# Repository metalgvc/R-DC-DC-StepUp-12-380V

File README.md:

Inverter 12v - 380v
Push-Pull 
TL494 module with MOSFET drivers
MOSFET IRF3205

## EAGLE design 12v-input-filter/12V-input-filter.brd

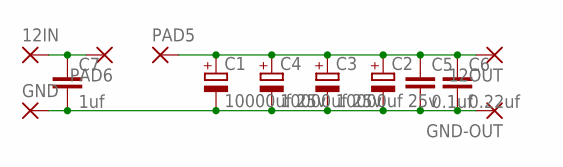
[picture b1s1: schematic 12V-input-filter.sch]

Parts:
12IN, 12OUT: 3,81/1,4
C1, C3, C4: 10000uf 25v; EB22,5D
C2: CPOL-EUE10-22.5; EB22,5D
C5: 0.1uf; C150-064X183
C6: 0.22uf; C150-064X183
C7: 1uf; C150-064X183
GND: 3,81/1,4
GND-OUT: 3,81/1,4
PAD5, PAD6: 3,81/1,4

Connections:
unnamed: C1.-, C2.-, C3.-, C4.-, C5.2, C6.2, C7.2, GND.1, GND-OUT.1
unnamed: 12OUT.1, C1.+, C2.+, C3.+, C4.+, C5.1, C6.1, PAD5.1
unnamed: 12IN.1, C7.1, PAD6.1

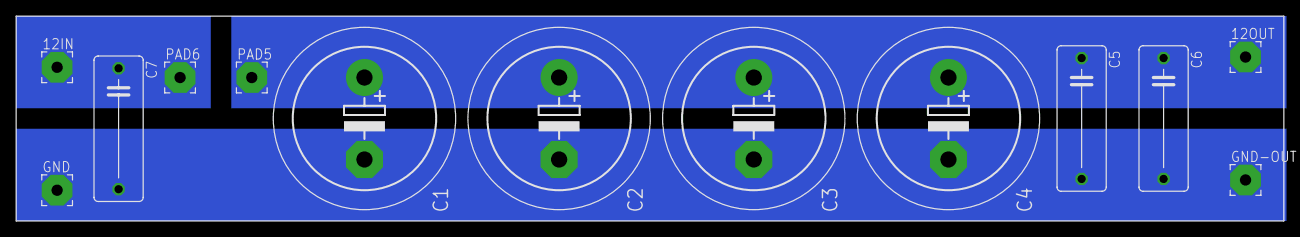
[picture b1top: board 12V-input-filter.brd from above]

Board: 2 copper layers, 157.2 x 25.4 mm, 13 parts (0 on the bottom side), 3 nets.

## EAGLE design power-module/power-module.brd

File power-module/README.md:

resistors 0.25W:
22 - 4
2k - 2

resistors 2W:
22 - 2
4k7 - 1
68k - 1

transistors:
IRF3205 - 4

diodes:
UF4007 - 4
shottky 60A300CT - 2

capacitors:
0.01uf (103) 400V - 2
0.1uf (104) 400V - 1
0.22uf (224) 400V(?) - 1

capacitors pol.:
470uf 200V - 4

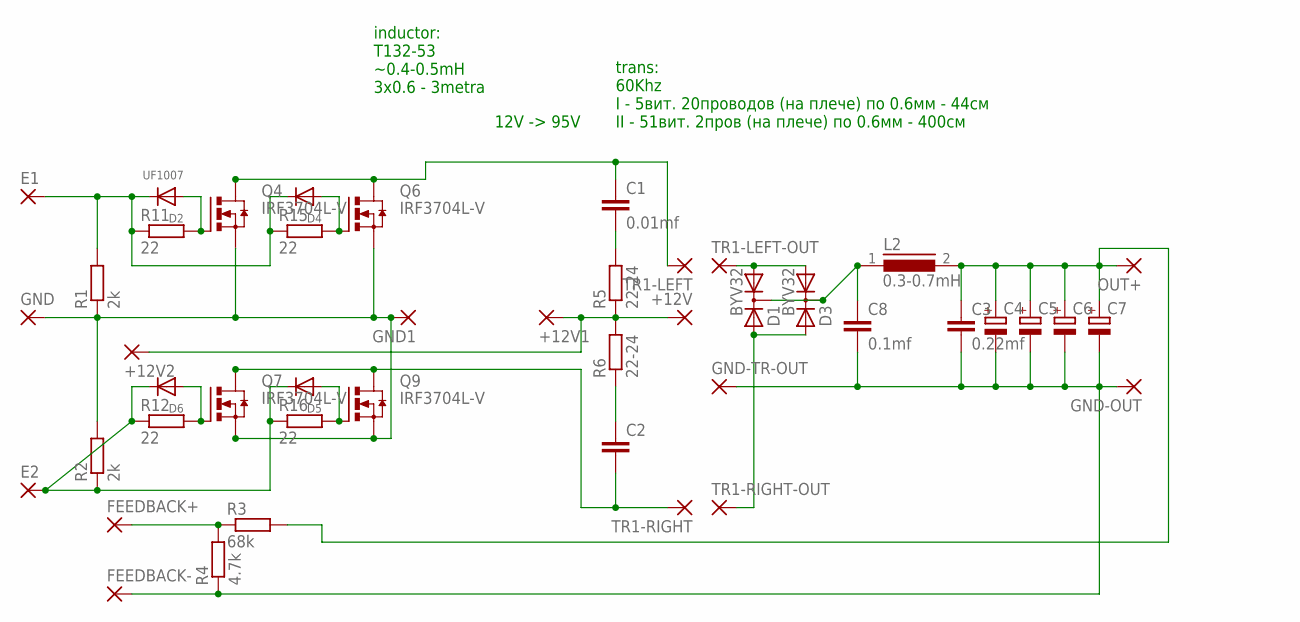
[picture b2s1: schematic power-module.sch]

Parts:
+12V, +12V1, +12V2: 3,81/1,1
C1: 0.01mf; C102-064X133
C2: C-EU102-064X133; C102-064X133
C3: 0.22mf; C150-064X183
C4, C5, C6, C7: CPOL-EUE10-22.5; EB22,5D
C8: 0.1mf; C150-064X183
D1, D3: BYV32; TO220ABS
D2: UF1007; DO-1N4148
D4, D5, D6: DIODEDO-1N4148; DO-1N4148
E1, E2: 3,81/1,1
FEEDBACK+: 3,81/1,1
FEEDBACK-: 3,81/1,1
GND, GND1: 3,81/1,1
GND-OUT: 3,81/1,1
GND-TR-OUT: 3,81/1,1
L2: 0.3-0.7mH; 11-27
OUT+: 3,81/1,1
Q4, Q6, Q7, Q9: IRF3704L-V; TO262-V
R1, R2: 2k; 0204/7
R3: 68k; 0617/17
R4: 4.7k; 0617/17
R5, R6: 22-24; P0613/15
R11, R12, R15, R16: 22; 0204/7
TR1-LEFT, TR1-LEFT-OUT, TR1-RIGHT, TR1-RIGHT-OUT: 3,81/1,1

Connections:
unnamed: GND.1, GND1.1, Q4.3 (S), Q6.3 (S), Q7.3 (S), Q9.3 (S), R1.1, R2.2
unnamed: C1.1, Q4.2 (D), Q6.2 (D), TR1-LEFT.1
unnamed: D5.C, D6.C, E2.1, R2.1, R12.1, R16.1
unnamed: FEEDBACK+.1, R3.1, R4.2
unnamed: +12V.1, +12V1.1, +12V2.1, R5.1, R6.2
unnamed: C3.2, C4.-, C5.-, C6.-, C7.-, C8.2, FEEDBACK-.1, GND-OUT.1, GND-TR-OUT.1, R4.1
unnamed: C2.2, Q7.2 (D), Q9.2 (D), TR1-RIGHT.1
unnamed: D2.C, D4.C, E1.1, R1.2, R11.1, R15.1
unnamed: C1.2, R5.2
unnamed: D1.A2, D3.A2, TR1-RIGHT-OUT.1
unnamed: C2.1, R6.1
unnamed: D1.A1, D3.A1, TR1-LEFT-OUT.1
unnamed: C8.1, D1.C, D3.C, L2.1
unnamed: C3.1, C4.+, C5.+, C6.+, C7.+, L2.2, OUT+.1, R3.2
unnamed: D2.A, Q4.1 (G), R11.2
unnamed: D6.A, Q7.1 (G), R12.2
unnamed: D4.A, Q6.1 (G), R15.2
unnamed: D5.A, Q9.1 (G), R16.2

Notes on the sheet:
12V -> 95V
trans: 60Khz I - 5вит. 20проводов (на плече) по 0.6мм - 44см II - 51вит. 2пров (на плече) по 0.6мм - 400см
inductor: T132-53 ~0.4-0.5mH 3x0.6 - 3metra

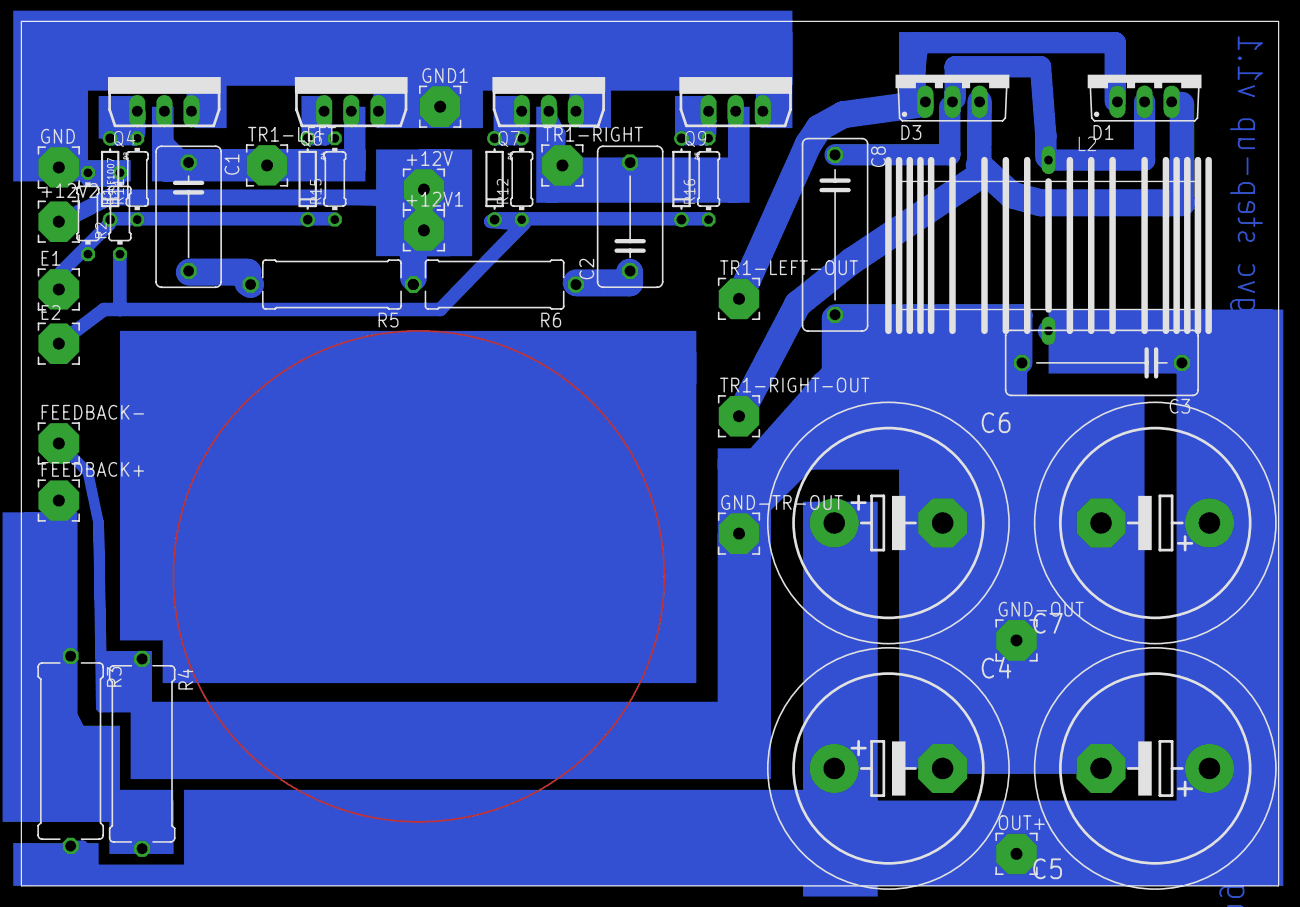
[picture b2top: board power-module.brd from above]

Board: 2 copper layers, 117.8 x 81.0 mm, 45 parts (0 on the bottom side), 18 nets.

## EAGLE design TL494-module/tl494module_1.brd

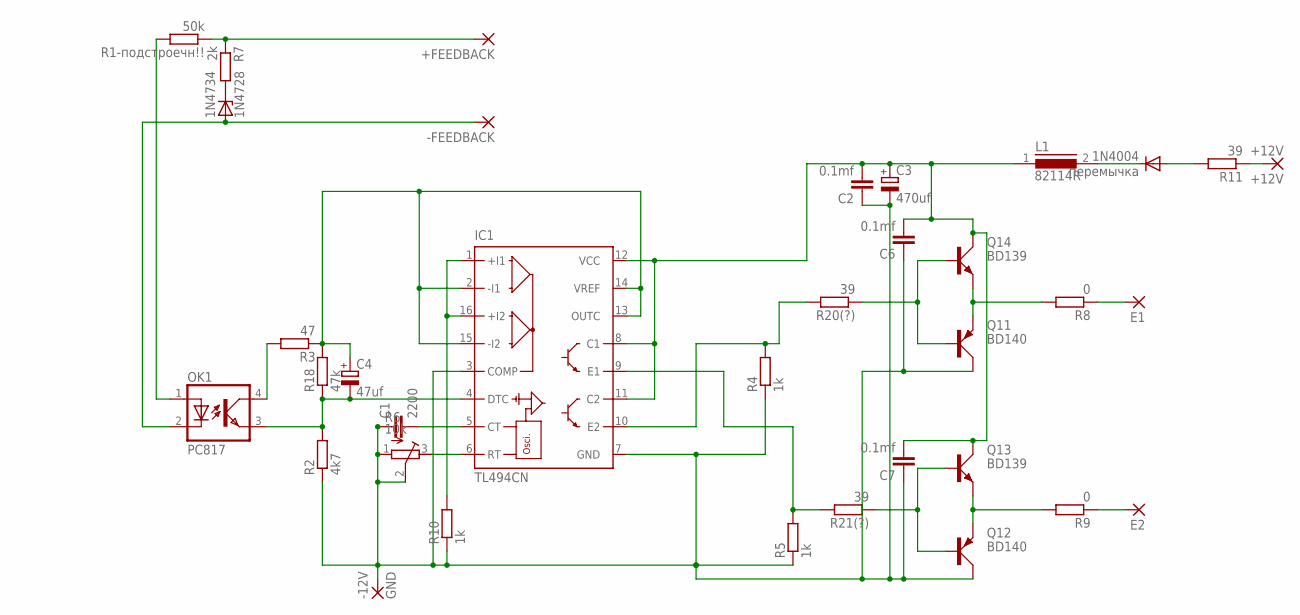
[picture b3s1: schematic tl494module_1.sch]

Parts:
1N4734: 1N4728; DO41Z10
+12V: +12V; 3,81/1,1
+FEEDBACK: 3,81/1,1
-12V: GND; 3,81/1,1
-FEEDBACK: 3,81/1,1
C1: 2200; C050-025X075
C2, C6, C7: 0.1mf; C050-025X075
C3: 470uf; E2-4
C4: 47uf; E2-4
E1, E2: 3,81/1,1
IC1: TL494CN; DIL16
L1: 82114R
OK1: PC817; DIL04
Q11, Q12: BD140; TO126AV
Q13, Q14: BD139; TO126AV
R1-подстроечн!!: 50k; 0204/7
R2: 4k7; 0204/7
R3: 47; 0204/7
R4, R5, R10: 1k; 0204/7
R6: 10k; RTRIM3296W
R7: 2k; 0204/7
R8, R9: 0; 0204/7
R11, R20(?), R21(?): 39; 0204/7
R18: 47k; 0204/7
перемычка: 1N4004; DO41-10

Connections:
unnamed: IC1.6 (RT), R6.3 (E)
unnamed: C1.2, IC1.5 (CT)
unnamed: +FEEDBACK.1, R1-подстроечн!!.1, R7.1
unnamed: IC1.1 (+I1), IC1.16 (+I2), R10.2
unnamed: 1N4734.C, R7.2
unnamed: IC1.10 (E2), R4.2, R20(?).2
unnamed: 1N4734.A, -FEEDBACK.1, OK1.2 (C)
unnamed: Q11.E, Q14.E, R8.2
unnamed: OK1.1 (A), R1-подстроечн!!.2
unnamed: IC1.9 (E1), R5.2, R21(?).2
unnamed: C4.+, IC1.2 (-I1), IC1.13 (OUTC), IC1.14 (VREF), IC1.15 (-I2), R3.1, R18.2
unnamed: E1.1, R8.1
unnamed: E2.1, R9.1
unnamed: C2.2, C3.+, C6.2, C7.2, IC1.8 (C1), IC1.11 (C2), IC1.12 (VCC), L1.1, Q13.C, Q14.C
unnamed: Q12.E, Q13.E, R9.2
unnamed: R11.2, перемычка.A
unnamed: C4.-, IC1.4 (DTC), OK1.3 (EMIT), R2.2, R18.1
unnamed: OK1.4 (COL), R3.2
unnamed: L1.2, перемычка.C
unnamed: -12V.1, C1.1, C2.1, C3.-, C6.1, C7.1, IC1.3 (COMP), IC1.7 (GND), Q11.C, Q12.C, R2.1, R4.1, R5.1, R6.1 (A), R6.2 (S), R10.1
unnamed: +12V.1, R11.1
unnamed: Q11.B, Q14.B, R20(?).1
unnamed: Q12.B, Q13.B, R21(?).1

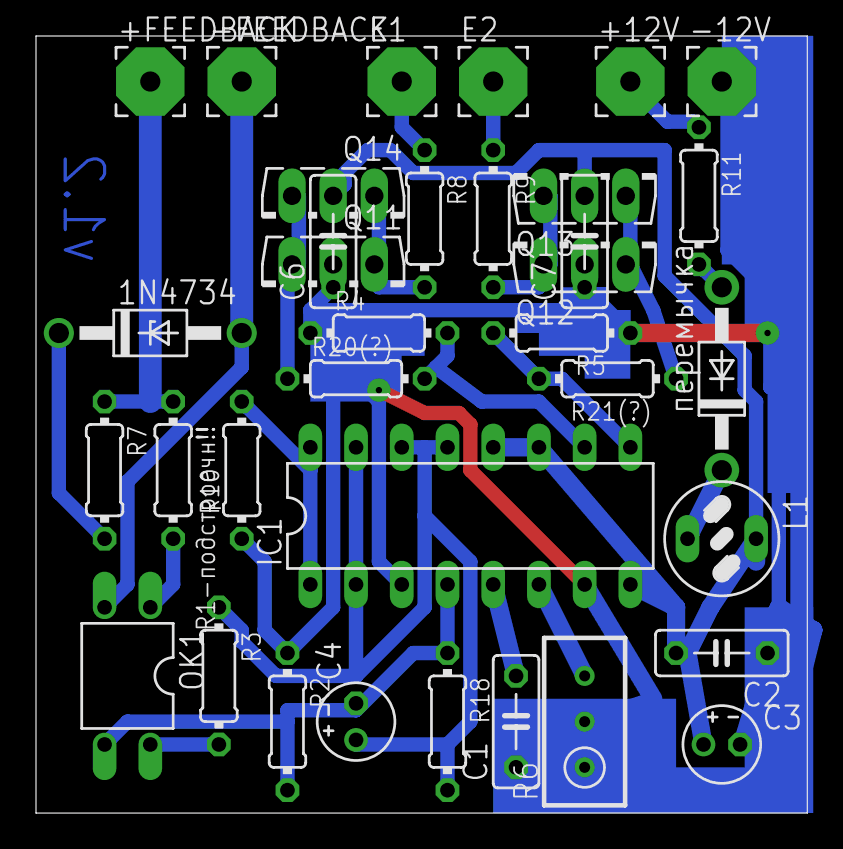
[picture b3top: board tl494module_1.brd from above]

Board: 2 copper layers, 42.9 x 43.2 mm, 35 parts (0 on the bottom side), 23 nets.

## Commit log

2019-01-02 init
